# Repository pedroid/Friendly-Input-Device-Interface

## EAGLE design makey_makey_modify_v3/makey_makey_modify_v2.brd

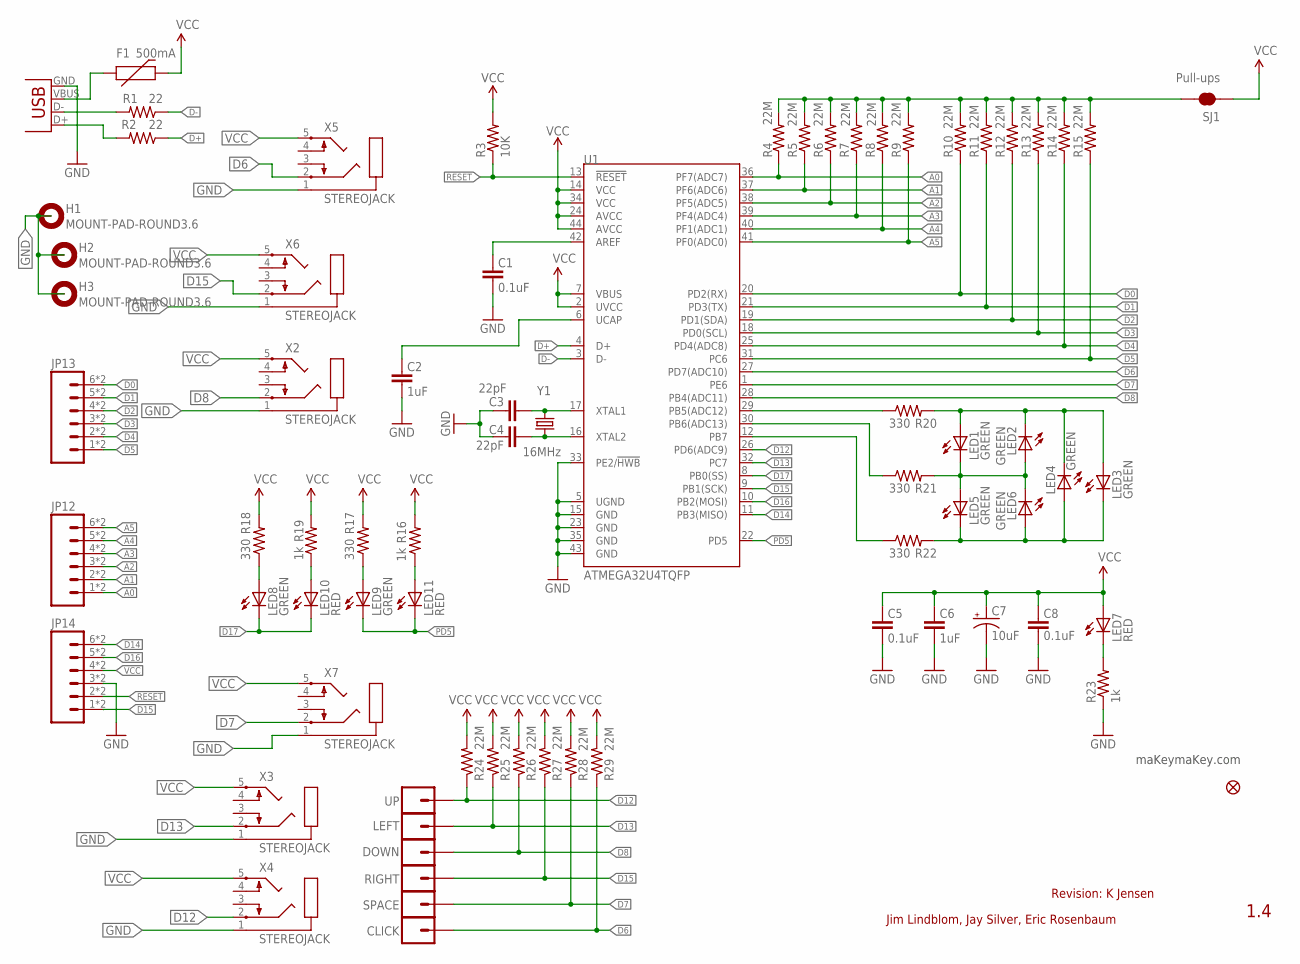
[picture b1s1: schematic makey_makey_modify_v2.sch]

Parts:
C1, C5, C8: 0.1uF; 0603-CAP
C2, C6: 1uF; 0603-CAP
C3, C4: 22pF; 0603-CAP
C7: 10uF; EIA3216
CLICK: M01ALLIGATOR-3MM; 1X01_ALLIGATOR_3MM
DOWN: M01ALLIGATOR-3MM; 1X01_ALLIGATOR_3MM
F1: 500mA; PTC-1206-WIDE
H1, H2, H3: MOUNT-PAD-ROUND3.6; 3,6-PAD
JP2: FIDUCIALUFIDUCIAL; MICRO-FIDUCIAL
JP12, JP13, JP14: M06SMD-STRAIGHT-COMBO; 1X06_SMD_STRAIGHT_COMBO
LED1, LED2, LED3, LED4, LED5, LED6: GREEN; LED-1206-BOTTOM
LED7, LED10, LED11: RED; LED-0603
LED8, LED9: GREEN; LED-0603
LEFT: M01ALLIGATOR-3MM; 1X01_ALLIGATOR_3MM
R1, R2: 22; 0603-RES
R3: 10K; 0603-RES
R4, R5, R6, R7, R8, R9, R10, R11, R12, R13, R14, R15, R24, R25, R26, R27, R28, R29: 22M; 0603-RES
R16, R19, R23: 1k; 0603-RES
R17, R18, R20, R21, R22: 330; 0603-RES
RIGHT: M01ALLIGATOR-3MM; 1X01_ALLIGATOR_3MM
SJ1: Pull-ups; SJ_2S-TRACE
SPACE: M01ALLIGATOR-3MM; 1X01_ALLIGATOR_3MM
U1: ATMEGA32U4TQFP; TQFP44
UP: M01ALLIGATOR-3MM; 1X01_ALLIGATOR_3MM
X1: USBSMD; USB-MINIB
X2, X3, X4, X5, X6, X7: STEREOJACK; STX3100
Y1: 16MHz; CRYSTAL-SMD-5X3

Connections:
A0: JP12.1, JP12.1-2 (1), R4.1, U1.36 (PF7(ADC7))
A1: JP12.2, JP12.2-2 (2), R5.1, U1.37 (PF6(ADC6))
A2: JP12.3, JP12.3-2 (3), R6.1, U1.38 (PF5(ADC5))
A3: JP12.4, JP12.4-2 (4), R7.1, U1.39 (PF4(ADC4))
A4: JP12.5, JP12.5-2 (5), R8.1, U1.40 (PF1(ADC1))
A5: JP12.6, JP12.6-2 (6), R9.1, U1.41 (PF0(ADC0))
AREF: C1.2, U1.42 (AREF)
D0: JP13.6, JP13.6-2 (6), R10.1, U1.20 (PD2(RX))
D1: JP13.5, JP13.5-2 (5), R11.1, U1.21 (PD3(TX))
D2: JP13.4, JP13.4-2 (4), R12.1, U1.19 (PD1(SDA))
D3: JP13.3, JP13.3-2 (3), R13.1, U1.18 (PD0(SCL))
D4: JP13.2, JP13.2-2 (2), R14.1, U1.25 (PD4(ADC8))
D5: JP13.1, JP13.1-2 (1), R15.1, U1.31 (PC6)
D6: CLICK.1@0, CLICK.1@2, R29.1, U1.27 (PD7(ADC10)), X5.2
D7: R28.1, SPACE.1@0, SPACE.1@2, U1.1 (PE6), X7.2
D8: DOWN.1@0, DOWN.1@2, R26.1, U1.28 (PB4(ADC11)), X2.2
D9: R20.1, U1.29 (PB5(ADC12))
D10: R21.1, U1.30 (PB6(ADC13))
D11: R22.1, U1.12 (PB7)
D12: R24.1, U1.26 (PD6(ADC9)), UP.1@0, UP.1@2, X4.2
D13: LEFT.1@0, LEFT.1@2, R25.1, U1.32 (PC7), X3.2
D14: JP14.6, JP14.6-2 (6), U1.11 (PB3(MISO))
D15: JP14.1, JP14.1-2 (1), R27.1, RIGHT.1@0, RIGHT.1@2, U1.9 (PB1(SCK)), X6.2
D16: JP14.5, JP14.5-2 (5), U1.10 (PB2(MOSI))
D17: LED8.C, LED10.C, U1.8 (PB0(SS))
D+: R2.1, U1.4 (D+)
D-: R1.1, U1.3 (D-)
GND: C1.1, C2.1, C3.2, C4.2, C5.1, C6.1, C7.C (-), C8.1, JP14.3, JP14.3-2 (3), R23.1, U1.5 (UGND), U1.15 (GND), U1.23 (GND), U1.33 (PE2/!HWB), U1.35 (GND), U1.43 (GND), X1.GND, X2.1, X3.1, X4.1, X5.1, X6.1, X7.1
unnamed: C4.1, U1.16 (XTAL2), Y1.1
unnamed: C3.1, U1.17 (XTAL1), Y1.3 (2)
unnamed: LED8.A, R18.1
unnamed: C2.2, U1.6 (UCAP)
unnamed: F1.1, X1.VBUS
unnamed: R1.2, X1.D-
unnamed: LED7.C, R23.2
unnamed: R2.2, X1.D+
unnamed: LED11.A, R16.1
unnamed: LED10.A, R19.1
unnamed: LED9.A, R17.1
unnamed: LED1.C, LED2.A, LED5.A, LED6.C, R21.2
unnamed: LED1.A, LED2.C, LED3.A, LED4.C, R20.2
unnamed: LED3.C, LED4.A, LED5.C, LED6.A, R22.2
PD5: LED9.C, LED11.C, U1.22 (PD5)
PULL-UP: R4.2, R5.2, R6.2, R7.2, R8.2, R9.2, R10.2, R11.2, R12.2, R13.2, R14.2, R15.2, SJ1.2
RESET: JP14.2, JP14.2-2 (2), R3.1, U1.13 (!RESET)
VCC: C5.2, C6.2, C7.A (+), C8.2, F1.2, JP14.4, JP14.4-2 (4), LED7.A, R3.2, R16.2, R17.2, R18.2, R19.2, R24.2, R25.2, R26.2, R27.2, R28.2, R29.2, SJ1.1, U1.2 (UVCC), U1.7 (VBUS), U1.14 (VCC), U1.24 (AVCC), U1.34 (VCC), U1.44 (AVCC), X2.5, X3.5, X4.5, X5.5, X6.5, X7.5

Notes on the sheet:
1.4
Jim Lindblom, Jay Silver, Eric Rosenbaum
maKeymaKey.com
Revision: K Jensen

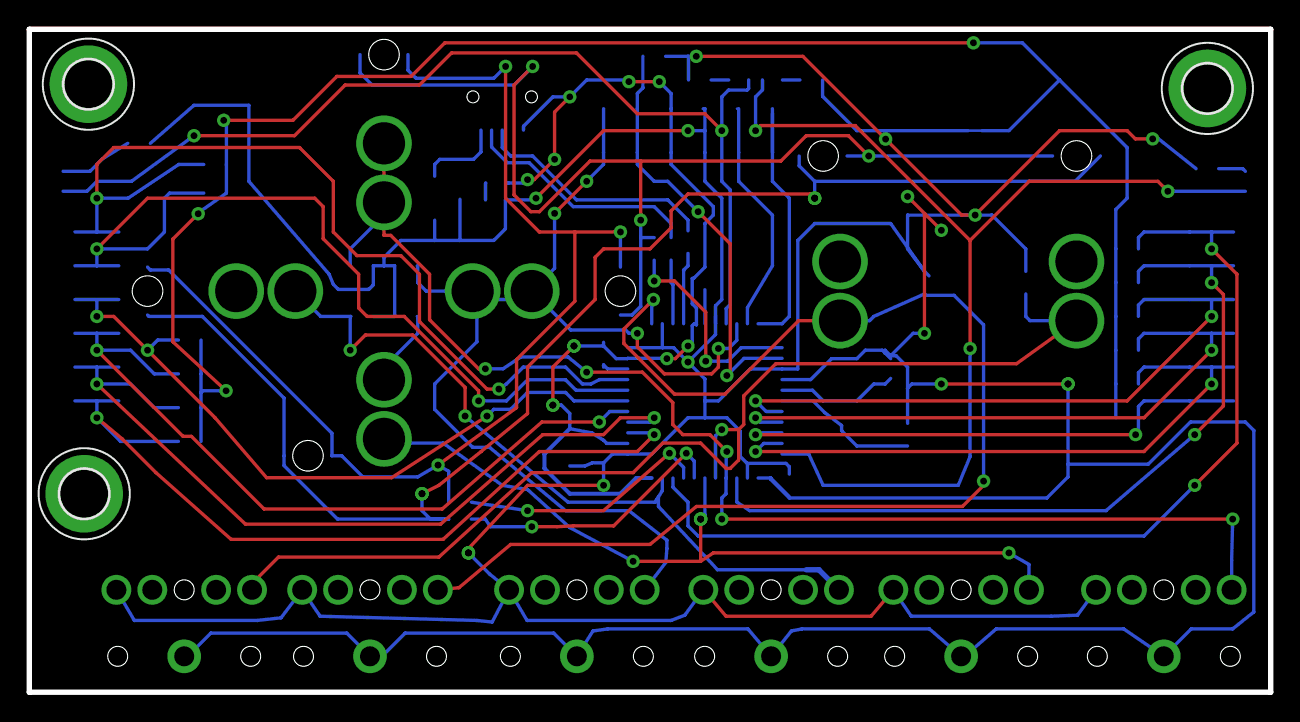
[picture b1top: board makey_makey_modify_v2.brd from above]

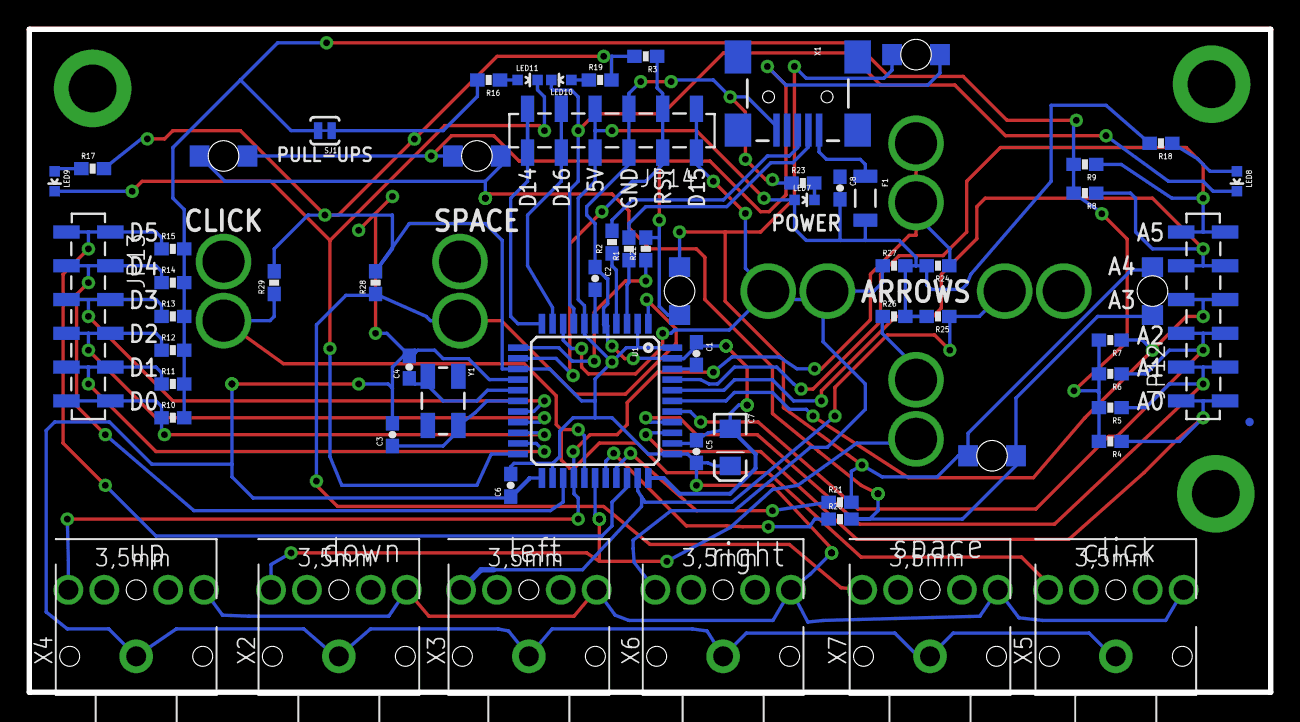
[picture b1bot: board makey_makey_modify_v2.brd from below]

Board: 2 copper layers, 93.3 x 49.8 mm, 72 parts (65 on the bottom side), 46 nets.

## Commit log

2015-10-24 :lollipop: Added .gitattributes & .gitignore files
2015-10-24 Initial
2015-10-24 rename from v2 to v3

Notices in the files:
parts and their libraries:
SparkFun-DigitalIC: Licensing: CC v3.0 Share-Alike You are welcome to use this library for commercial purposes.
SparkFun-Aesthetics: Released under the Creative Commons
SparkFun-Aesthetics: http://creativecommons.org/licenses/by-sa/3.0
